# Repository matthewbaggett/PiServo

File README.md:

PiServo
=======

Raspberry Pi Servo Motor Controller

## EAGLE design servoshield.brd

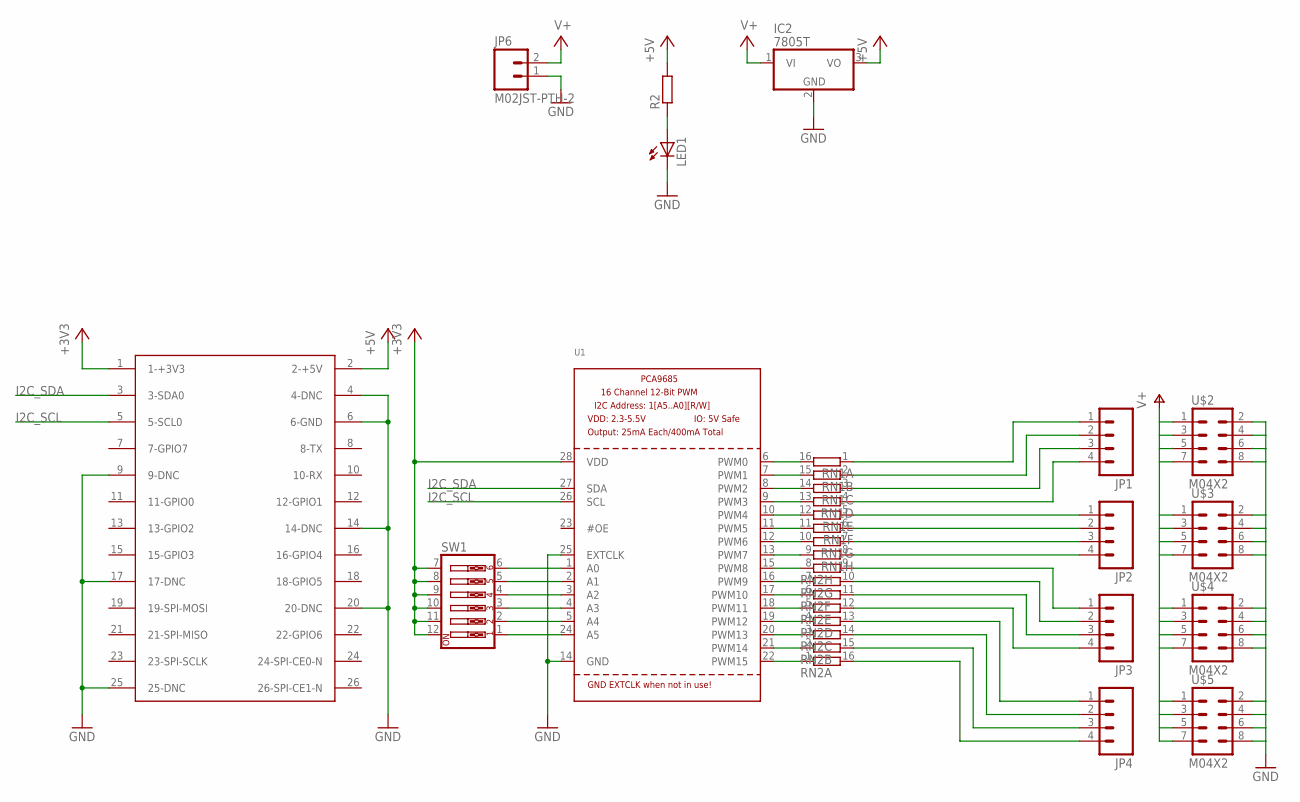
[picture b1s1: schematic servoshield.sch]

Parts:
IC2: 7805T; TO220H
JP1, JP2, JP3, JP4: M04PTH; 1X04
JP6: M02JST-PTH-2; JST-2-PTH
LED1: LED3MM
R2: R-EU_0207/7; 0207/7
RN1, RN2: 8R-N; DIL16
SW1: SW_DIP-6; EDG-06
U1: PCA9685; TSSOP28
U$1: RASPBERRY-PI
U$2, U$3, U$4, U$5: M04X2; 2X4

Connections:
+3V3: SW1.7, SW1.8, SW1.9, SW1.10, SW1.11, SW1.12, U1.28 (VDD), U$1.1 (1-+3V3)
+5V: IC2.3 (VO), R2.2, U$1.2 (2-+5V)
GND: IC2.2 (GND), JP6.1, LED1.K (C), U1.14 (GND), U1.25 (EXTCLK), U$1.4 (4-DNC), U$1.6 (6-GND), U$1.9 (9-DNC), U$1.14 (14-DNC), U$1.17 (17-DNC), U$1.20 (20-DNC), U$1.25 (25-DNC), U$2.2, U$2.4, U$2.6, U$2.8, U$3.2, U$3.4, U$3.6, U$3.8, U$4.2, U$4.4, U$4.6, U$4.8, U$5.2, U$5.4, U$5.6, U$5.8
I2C_SCL: U1.26 (SCL), U$1.5 (5-SCL0)
I2C_SDA: U1.27 (SDA), U$1.3 (3-SDA0)
unnamed: RN2.7 (1), U1.16 (PWM9)
unnamed: RN2.8 (1), U1.15 (PWM8)
unnamed: RN1.9 (2), U1.13 (PWM7)
unnamed: RN2.1, U1.22 (PWM15)
unnamed: JP1.4, RN1.4 (1)
unnamed: JP1.3, RN1.3 (1)
unnamed: JP1.2, RN1.2 (1)
unnamed: JP1.1, RN1.1
unnamed: JP3.1, RN2.9 (2)
unnamed: JP3.2, RN2.10 (2)
unnamed: SW1.1, U1.24 (A5)
unnamed: SW1.2, U1.5 (A4)
unnamed: SW1.3, U1.4 (A3)
unnamed: SW1.4, U1.3 (A2)
unnamed: SW1.5, U1.2 (A1)
unnamed: SW1.6, U1.1 (A0)
unnamed: JP3.3, RN2.11 (2)
unnamed: JP3.4, RN2.12 (2)
unnamed: JP4.1, RN2.13 (2)
unnamed: JP4.2, RN2.14 (2)
unnamed: JP4.3, RN2.15 (2)
unnamed: JP4.4, RN2.16 (2)
unnamed: RN2.2 (1), U1.21 (PWM14)
unnamed: RN2.3 (1), U1.20 (PWM13)
unnamed: RN2.4 (1), U1.19 (PWM12)
unnamed: RN2.5 (1), U1.18 (PWM11)
unnamed: RN2.6 (1), U1.17 (PWM10)
unnamed: RN1.10 (2), U1.12 (PWM6)
unnamed: RN1.11 (2), U1.11 (PWM5)
unnamed: RN1.12 (2), U1.10 (PWM4)
unnamed: RN1.13 (2), U1.9 (PWM3)
unnamed: RN1.14 (2), U1.8 (PWM2)
unnamed: RN1.15 (2), U1.7 (PWM1)
unnamed: RN1.16 (2), U1.6 (PWM0)
unnamed: JP2.1, RN1.5 (1)
unnamed: JP2.4, RN1.8 (1)
unnamed: JP2.3, RN1.7 (1)
unnamed: JP2.2, RN1.6 (1)
unnamed: LED1.A, R2.1
V+: IC2.1 (VI), JP6.2, U$2.1, U$2.3, U$2.5, U$2.7, U$3.1, U$3.3, U$3.5, U$3.7, U$4.1, U$4.3, U$4.5, U$4.7, U$5.1, U$5.3, U$5.5, U$5.7

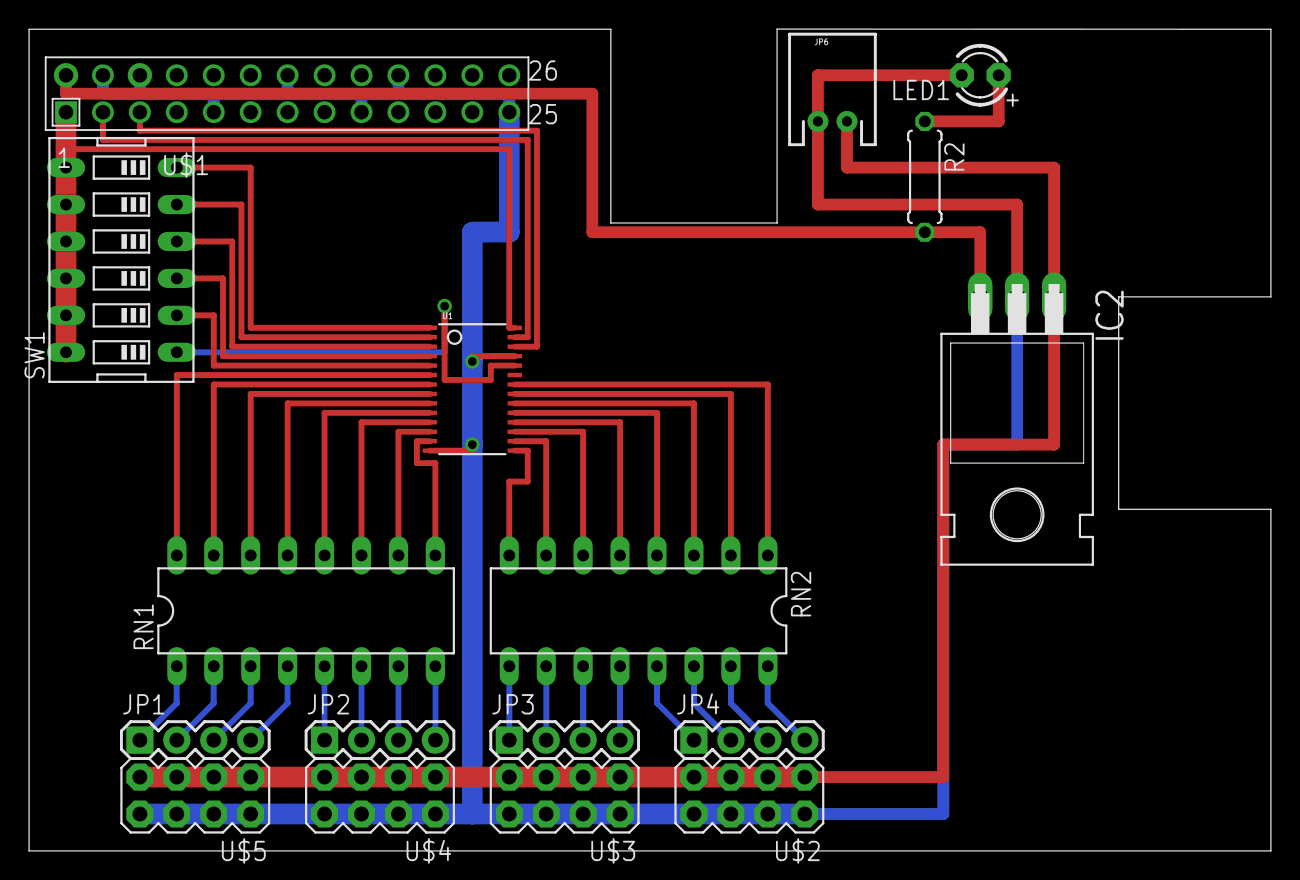
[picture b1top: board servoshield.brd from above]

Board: 2 copper layers, 85.4 x 56.5 mm, 17 parts (0 on the bottom side), 45 nets.

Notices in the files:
parts and their libraries:
SparkFun-Connectors: Licensing: Creative Commons ShareAlike 4.0 International - https://creativecommons.org/licenses/by-sa/4.0
